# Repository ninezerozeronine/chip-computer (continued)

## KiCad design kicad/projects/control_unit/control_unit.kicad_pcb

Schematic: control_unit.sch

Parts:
C1, C2, C3, C4, C5, C6, C7, C8, C9: 100nF; C_Disc_D4.7mm_W2.5mm_P5.00mm
J1: BUS; PinHeader_1x11_P2.54mm_Horizontal
J2: FLAGS; PinSocket_1x04_P2.54mm_Horizontal
J3: INSTRUCTION; PinSocket_1x08_P2.54mm_Horizontal
J4: BACKPLANE; backplane-connector
J5: MIR INST LEDS; PinSocket_1x16_P2.54mm_Horizontal
J6: STEP LEDS; PinSocket_1x16_P2.54mm_Horizontal
J7: MIR FLAG LEDS; PinSocket_1x08_P2.54mm_Horizontal
J8: STEP RESET; SolderWirePad_1x01_Drill0.8mm
J9: MASTER RESET; PinSocket_1x01_P2.54mm_Horizontal
RN1: MIR INST RESISTORS; R_Array_SIP9
RN2: STEP RESISTORS; R_Array_SIP9
RN3: MIR FLAG RESISTORS; R_Array_SIP5
U1, U2, U3, U4: 28C256; DIP-28_W15.24mm_Socket
U5: 74HCT377; DIP-20_W7.62mm_Socket
U6: 74HCT161; DIP-16_W7.62mm_Socket
U7: 74HCT173; DIP-16_W7.62mm_Socket
U8: 74HCT138; DIP-16_W7.62mm_Socket
U9: 74HCT04; DIP-14_W7.62mm_Socket

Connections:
/CONTROL_CLOCK: J4.34, U5.11 (CP), U6.2 (CP), U7.7 (CP)
/MASTER_RESET: J1.11
/MC_STEP_0: U1.10 (A0), U2.10 (A0), U3.10 (A0), U4.10 (A0), U6.14 (Q0), U8.1 (A)
/MC_STEP_1: U1.9 (A1), U2.9 (A1), U3.9 (A1), U4.9 (A1), U6.13 (Q1), U8.2 (B)
/MC_STEP_2: U1.8 (A2), U2.8 (A2), U3.8 (A2), U4.8 (A2), U6.12 (Q2), U8.3 (C)
/MIR_FLAG_C: J7.5, U1.5 (A5), U2.5 (A5), U3.5 (A5), U4.5 (A5), U7.5 (Q2)
/MIR_FLAG_E: J7.7, U1.4 (A6), U2.4 (A6), U3.4 (A6), U4.4 (A6), U7.6 (Q3)
/MIR_FLAG_N: J7.3, U1.6 (A4), U2.6 (A4), U3.6 (A4), U4.6 (A4), U7.4 (Q1)
/MIR_FLAG_Z: J7.1, U1.7 (A3), U2.7 (A3), U3.7 (A3), U4.7 (A3), U7.3 (Q0)
/MIR_INST_0: J5.1, U1.3 (A7), U2.3 (A7), U3.3 (A7), U4.3 (A7), U5.2 (Q0)
/MIR_INST_1: J5.3, U1.25 (A8), U2.25 (A8), U3.25 (A8), U4.25 (A8), U5.5 (Q1)
/MIR_INST_2: J5.5, U1.24 (A9), U2.24 (A9), U3.24 (A9), U4.24 (A9), U5.6 (Q2)
/MIR_INST_3: J5.7, U1.21 (A10), U2.21 (A10), U3.21 (A10), U4.21 (A10), U5.9 (Q3)
/MIR_INST_4: J5.9, U1.23 (A11), U2.23 (A11), U3.23 (A11), U4.23 (A11), U5.12 (Q4)
/MIR_INST_5: J5.11, U1.2 (A12), U2.2 (A12), U3.2 (A12), U4.2 (A12), U5.15 (Q5)
/MIR_INST_6: J5.13, U1.26 (A13), U2.26 (A13), U3.26 (A13), U4.26 (A13), U5.16 (Q6)
/MIR_INST_7: J5.15, U1.1 (A14), U2.1 (A14), U3.1 (A14), U4.1 (A14), U5.19 (Q7)
/ROM_0_0: J4.1, U1.11 (D0)
/ROM_0_1: J4.2, U1.12 (D1)
/ROM_0_2: J4.3, U1.13 (D2)
/ROM_0_3: J4.4, U1.15 (D3)
/ROM_0_4: J4.5, U1.16 (D4)
/ROM_0_5: J4.6, U1.17 (D5)
/ROM_0_6: J4.7, U1.18 (D6)
/ROM_0_7: J4.8, U1.19 (D7)
/ROM_1_0: J4.9, U2.11 (D0)
/ROM_1_1: J4.10, U2.12 (D1)
/ROM_1_2: J4.11, U2.13 (D2)
/ROM_1_3: J4.12, U2.15 (D3)
/ROM_1_4: J4.13, U2.16 (D4)
/ROM_1_5: J4.14, U2.17 (D5)
/ROM_1_6: J4.15, U2.18 (D6)
/ROM_1_7: J4.16, U2.19 (D7)
/ROM_2_0: J4.17, U3.11 (D0)
/ROM_2_1: J4.18, U3.12 (D1)
/ROM_2_2: J4.19, U3.13 (D2)
/ROM_2_3: J4.20, U3.15 (D3)
/ROM_2_4: J4.21, U3.16 (D4)
/ROM_2_5: J4.22, U3.17 (D5)
/ROM_2_6: J4.23, U3.18 (D6)
/ROM_2_7: J4.24, U3.19 (D7)
/ROM_3_0: J4.25, U4.11 (D0)
/ROM_3_1: J4.26, U4.12 (D1)
/ROM_3_2: J4.27, U4.13 (D2)
/ROM_3_3: J4.28, U4.15 (D3)
/ROM_3_4: J4.29, U4.16 (D4)
/ROM_3_5: J4.30, U4.17 (D5)
/ROM_3_6: J4.31, U4.18 (D6)
/ROM_3_7: J4.32, U4.19 (D7)
GND: C1.1, C2.2, C3.1, C4.2, C5.1, C6.2, C7.2, C8.2, C9.2, J1.10, RN1.1 (common), RN3.1 (common), U1.14 (GND), U1.20 (~CS), U1.22 (~OE), U2.14 (GND), U2.20 (~CS), U2.22 (~OE), U3.14 (GND), U3.20 (~CS), U3.22 (~OE), U4.14 (GND), U4.20 (~CS), U4.22 (~OE), U5.1 (~E), U5.10 (GND), U6.3 (P0), U6.4 (P1), U6.5 (P2), U6.6 (P3), U6.8 (GND), U7.1 (~OE), U7.2 (~OE2), U7.8 (GND), U7.9 (~E1), U7.10 (~E2), U7.15 (MR), U8.4 (~G2A), U8.5 (~G2B), U8.8 (GND), U9.5, U9.7 (GND), U9.9, U9.11, U9.13
unnamed: J2.1, U7.14 (D0)
unnamed: J2.2, U7.13 (D1)
unnamed: J2.3, U7.12 (D2)
unnamed: J2.4, U7.11 (D3)
unnamed: J3.1, U5.3 (D0)
unnamed: J3.2, U5.4 (D1)
unnamed: J3.3, U5.7 (D2)
unnamed: J3.4, U5.8 (D3)
unnamed: J3.5, U5.13 (D4)
unnamed: J3.6, U5.14 (D5)
unnamed: J3.7, U5.17 (D6)
unnamed: J3.8, U5.18 (D7)
unnamed: J5.2, RN1.2 (R1)
unnamed: J5.4, RN1.3 (R2)
unnamed: J5.6, RN1.4 (R3)
unnamed: J5.8, RN1.5 (R4)
unnamed: J5.10, RN1.6 (R5)
unnamed: J5.12, RN1.7 (R6)
unnamed: J5.14, RN1.8 (R7)
unnamed: J5.16, RN1.9 (R8)
unnamed: J6.1, U8.15 (Y0)
unnamed: J6.2, RN2.2 (R1)
unnamed: J6.3, U8.14 (Y1)
unnamed: J6.4, RN2.3 (R2)
unnamed: J6.5, U8.13 (Y2)
unnamed: J6.6, RN2.4 (R3)
unnamed: J6.7, U8.12 (Y3)
unnamed: J6.8, RN2.5 (R4)
unnamed: J6.9, U8.11 (Y4)
unnamed: J6.10, RN2.6 (R5)
unnamed: J6.11, U8.10 (Y5)
unnamed: J6.12, RN2.7 (R6)
unnamed: J6.13, U8.9 (Y6)
unnamed: J6.14, RN2.8 (R7)
unnamed: J6.15, U8.7 (Y7)
unnamed: J6.16, RN2.9 (R8)
unnamed: J7.2, RN3.2 (R1)
unnamed: J7.4, RN3.3 (R2)
unnamed: J7.6, RN3.4 (R3)
unnamed: J7.8, RN3.5 (R4)
unnamed: J8.1, U9.3
unnamed: J9.1, U9.1
unnamed: U6.1 (~MR), U9.2
unnamed: U6.9 (~SPE), U9.4
VCC: C1.2, C2.1, C3.2, C4.1, C5.2, C6.1, C7.1, C8.1, C9.1, J1.9, RN2.1 (common), U1.27 (~WE), U1.28 (VCC), U2.27 (~WE), U2.28 (VCC), U3.27 (~WE), U3.28 (VCC), U4.27 (~WE), U4.28 (VCC), U5.20 (VCC), U6.7 (PE), U6.10 (TE), U6.16 (VCC), U7.16 (VCC), U8.6 (G1), U8.16 (VCC), U9.14 (VCC)

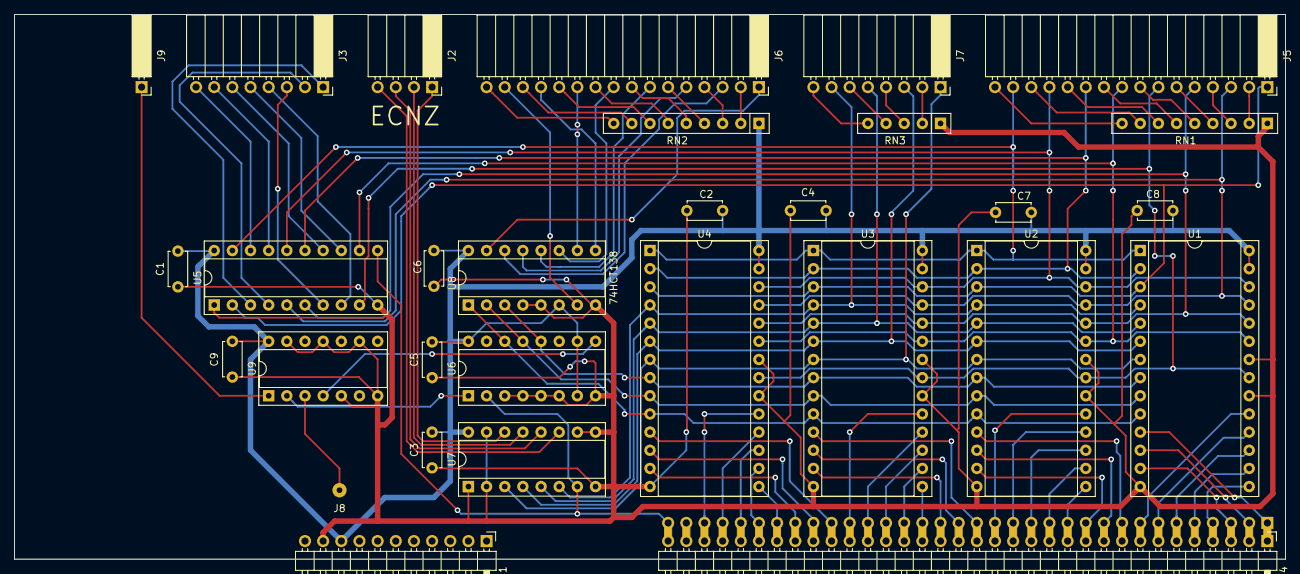
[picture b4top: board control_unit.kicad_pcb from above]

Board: 2 copper layers, 177.8 x 76.2 mm, 30 parts (0 on the bottom side), 94 nets.

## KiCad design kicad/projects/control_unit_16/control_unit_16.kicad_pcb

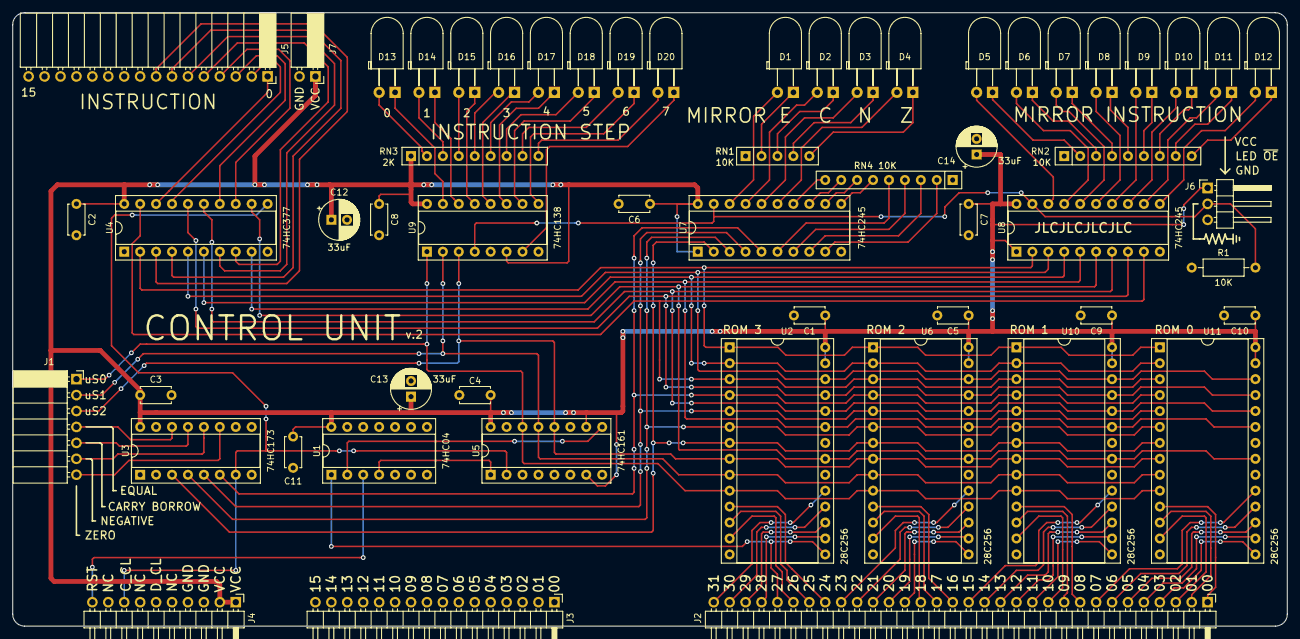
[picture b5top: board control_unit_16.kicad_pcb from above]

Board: 2 copper layers, 203.2 x 97.8 mm, 57 parts (0 on the bottom side), 114 nets.

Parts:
C1, C2, C3, C4, C5, C6, C7, C8, C9, C10, C11: 0.1uF; C_Disc_D4.7mm_W2.5mm_P5.00mm
C12, C13, C14: 33uF; CP_Radial_D6.3mm_P2.50mm
D1, D2, D3, D4, D5, D6, D7, D8, D9, D10, D11, D12, D13, D14, D15, D16, D17, D18, D19, D20: LED; LED_D5.0mm_Horizontal_O3.81mm_Z3.0mm
J1: Conn_01x04_Female; PinSocket_1x07_P2.54mm_Horizontal
J2: Control_signal_backplane; backplane-connector-single-row
J3: Bus_connection; bus-connection
J4: Aux_connection; aux-connection
J5: Conn_01x16_Female; PinSocket_1x16_P2.54mm_Horizontal
J6: LED_CONTROL; PinHeader_1x03_P2.54mm_Horizontal
J7: TOP_POWER; PinSocket_1x02_P2.54mm_Horizontal
R1: 10K; R_Axial_DIN0207_L6.3mm_D2.5mm_P10.16mm_Horizontal
RN1: 10K; R_Array_SIP5
RN2, RN4: 10K; R_Array_SIP9
RN3: 2K; R_Array_SIP9
U1: 74HC04; DIP-14_W7.62mm_Socket
U2, U6, U10, U11: 28C256; DIP-28_W15.24mm_Socket
U3: 74HC173; DIP-16_W7.62mm_Socket
U4: 74HC377; DIP-20_W7.62mm_Socket
U5: 74HC161; DIP-16_W7.62mm_Socket
U7, U8: 74HC245; DIP-20_W7.62mm_Socket
U9: 74HC138; DIP-16_W7.62mm_Socket

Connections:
/BIN_STEP_0: J1.1, U2.10, U5.14, U6.10, U9.1, U10.10, U11.10
/BIN_STEP_1: J1.2, U2.9, U5.13, U6.9, U9.2, U10.9, U11.9
/BIN_STEP_2: J1.3, U2.8, U5.12, U6.8, U9.3, U10.8, U11.8
/CARRY: J1.5, U3.13
/CONTROL_CLOCK: J4.8, U3.7, U4.11, U5.2
/EQUAL: J1.4, U3.14
/INST_00: J5.1, U4.18
/INST_01: J5.2, U4.17
/INST_02: J5.3, U4.14
/INST_03: J5.4, U4.13
/INST_04: J5.5, U4.8
/INST_05: J5.6, U4.7
/INST_06: J5.7, U4.4
/INST_07: J5.8, U4.3
/LED_CONTROL: J6.2, R1.2, U7.19, U8.19, U9.4
/LIN_STEP_0: D13.1, U9.15
/LIN_STEP_1: D14.1, U9.14
/LIN_STEP_2: D15.1, U9.13
/LIN_STEP_3: D16.1, U9.12
/LIN_STEP_4: D17.1, U9.11
/LIN_STEP_5: D18.1, U9.10
/LIN_STEP_6: D19.1, U9.9
/LIN_STEP_7: D20.1, U9.7
/MIR_CARRY: U2.6, U3.4, U6.6, U7.3, U10.6, U11.6
/MIR_EQUAL: U2.7, U3.3, U6.7, U7.2, U10.7, U11.7
/MIR_INST_0: U2.3, U4.19, U6.3, U8.9, U10.3, U11.3
/MIR_INST_1: U2.25, U4.16, U6.25, U8.8, U10.25, U11.25
/MIR_INST_2: U2.24, U4.15, U6.24, U8.7, U10.24, U11.24
/MIR_INST_3: U2.21, U4.12, U6.21, U8.6, U10.21, U11.21
/MIR_INST_4: U2.23, U4.9, U6.23, U8.5, U10.23, U11.23
/MIR_INST_5: U2.2, U4.6, U6.2, U8.4, U10.2, U11.2
/MIR_INST_6: U2.26, U4.5, U6.26, U8.3, U10.26, U11.26
/MIR_INST_7: U2.1, U4.2, U6.1, U8.2, U10.1, U11.1
/MIR_NEGATIVE: U2.5, U3.5, U6.5, U7.4, U10.5, U11.5
/MIR_ZERO: U2.4, U3.6, U6.4, U7.5, U10.4, U11.4
/NEGATIVE: J1.6, U3.12
/RESET: J4.10, U1.3
/ROM_0_0: J2.1, U11.11
/ROM_0_1: J2.2, U11.12
/ROM_0_2: J2.3, U11.13
/ROM_0_3: J2.4, U11.15
/ROM_0_4: J2.5, U11.16
/ROM_0_5: J2.6, U11.17
/ROM_0_6: J2.7, U11.18
/ROM_0_7: J2.8, U11.19
/ROM_1_0: J2.9, U10.11
/ROM_1_1: J2.10, U10.12
/ROM_1_2: J2.11, U10.13
/ROM_1_3: J2.12, U10.15
/ROM_1_4: J2.13, U10.16
/ROM_1_5: J2.14, U10.17
/ROM_1_6: J2.15, U10.18
/ROM_1_7: J2.16, U10.19
/ROM_2_0: J2.17, U6.11
/ROM_2_1: J2.18, U6.12
/ROM_2_2: J2.19, U6.13
/ROM_2_3: J2.20, U6.15
/ROM_2_4: J2.21, U6.16
/ROM_2_5: J2.22, U6.17
/ROM_2_6: J2.23, U6.18
/ROM_2_7: J2.24, U6.19
/ROM_3_0: J2.25, U2.11
/ROM_3_1: J2.26, U2.12
/ROM_3_2: J2.27, U2.13
/ROM_3_4: J2.29, U2.16
/ROM_3_5: J2.30, U2.17
/ROM_3_6: J2.31, U2.18
/ROM_3_7: J2.32, U2.19
/STEP_RESET: J2.28, U1.1, U2.15
/ZERO: J1.7, U3.11
/~RESET: U1.4, U5.1
/~STEP_RESET: U1.2, U5.9
GND: C1.2, C2.2, C3.2, C4.2, C5.2, C6.2, C7.2, C8.2, C9.2, C10.2, C11.2, C12.2, C13.2, C14.2, J4.3, J4.4, J6.3, J7.2, R1.1, RN1.1, RN2.1, RN4.1, U1.5, U1.7, U1.9, U1.11, U1.13, U2.14, U2.20, U2.22, U3.1, U3.2, U3.8, U3.9, U3.10, U3.15, U4.1, U4.10, U5.3, U5.4, U5.5, U5.6, U5.8, U6.14, U6.20, U6.22, U7.10, U8.10, U9.5, U9.8, U10.14, U10.20, U10.22, U11.14, U11.20, U11.22
unnamed: D1.1, RN1.2
unnamed: D1.2, U7.18
unnamed: D2.1, RN1.3
unnamed: D2.2, U7.17
unnamed: D3.1, RN1.4
unnamed: D3.2, U7.16
unnamed: D4.1, RN1.5
unnamed: D4.2, U7.15
unnamed: D5.1, RN2.2
unnamed: D5.2, U8.18
unnamed: D6.1, RN2.3
unnamed: D6.2, U8.17
unnamed: D7.1, RN2.4
unnamed: D7.2, U8.16
unnamed: D8.1, RN2.5
unnamed: D8.2, U8.15
unnamed: D9.1, RN2.6
unnamed: D9.2, U8.14
unnamed: D10.1, RN2.7
unnamed: D10.2, U8.13
unnamed: D11.1, RN2.8
unnamed: D11.2, U8.12
unnamed: D12.1, RN2.9
unnamed: D12.2, U8.11
unnamed: D13.2, RN3.2
unnamed: D14.2, RN3.3
unnamed: D15.2, RN3.4
unnamed: D16.2, RN3.5
unnamed: D17.2, RN3.6
unnamed: D18.2, RN3.7
unnamed: D19.2, RN3.8
unnamed: D20.2, RN3.9
unnamed: RN4.2, U7.9
unnamed: RN4.3, U7.8
unnamed: RN4.4, U7.7
unnamed: RN4.5, U7.6
unnamed: RN4.6, U7.11
unnamed: RN4.7, U7.12
unnamed: RN4.8, U7.13
unnamed: RN4.9, U7.14
VCC: C1.1, C2.1, C3.1, C4.1, C5.1, C6.1, C7.1, C8.1, C9.1, C10.1, C11.1, C12.1, C13.1, C14.1, J4.1, J4.2, J6.1, J7.1, RN3.1, U1.14, U2.27, U2.28, U3.16, U4.20, U5.7, U5.10, U5.16, U6.27, U6.28, U7.1, U7.20, U8.1, U8.20, U9.6, U9.16, U10.27, U10.28, U11.27, U11.28

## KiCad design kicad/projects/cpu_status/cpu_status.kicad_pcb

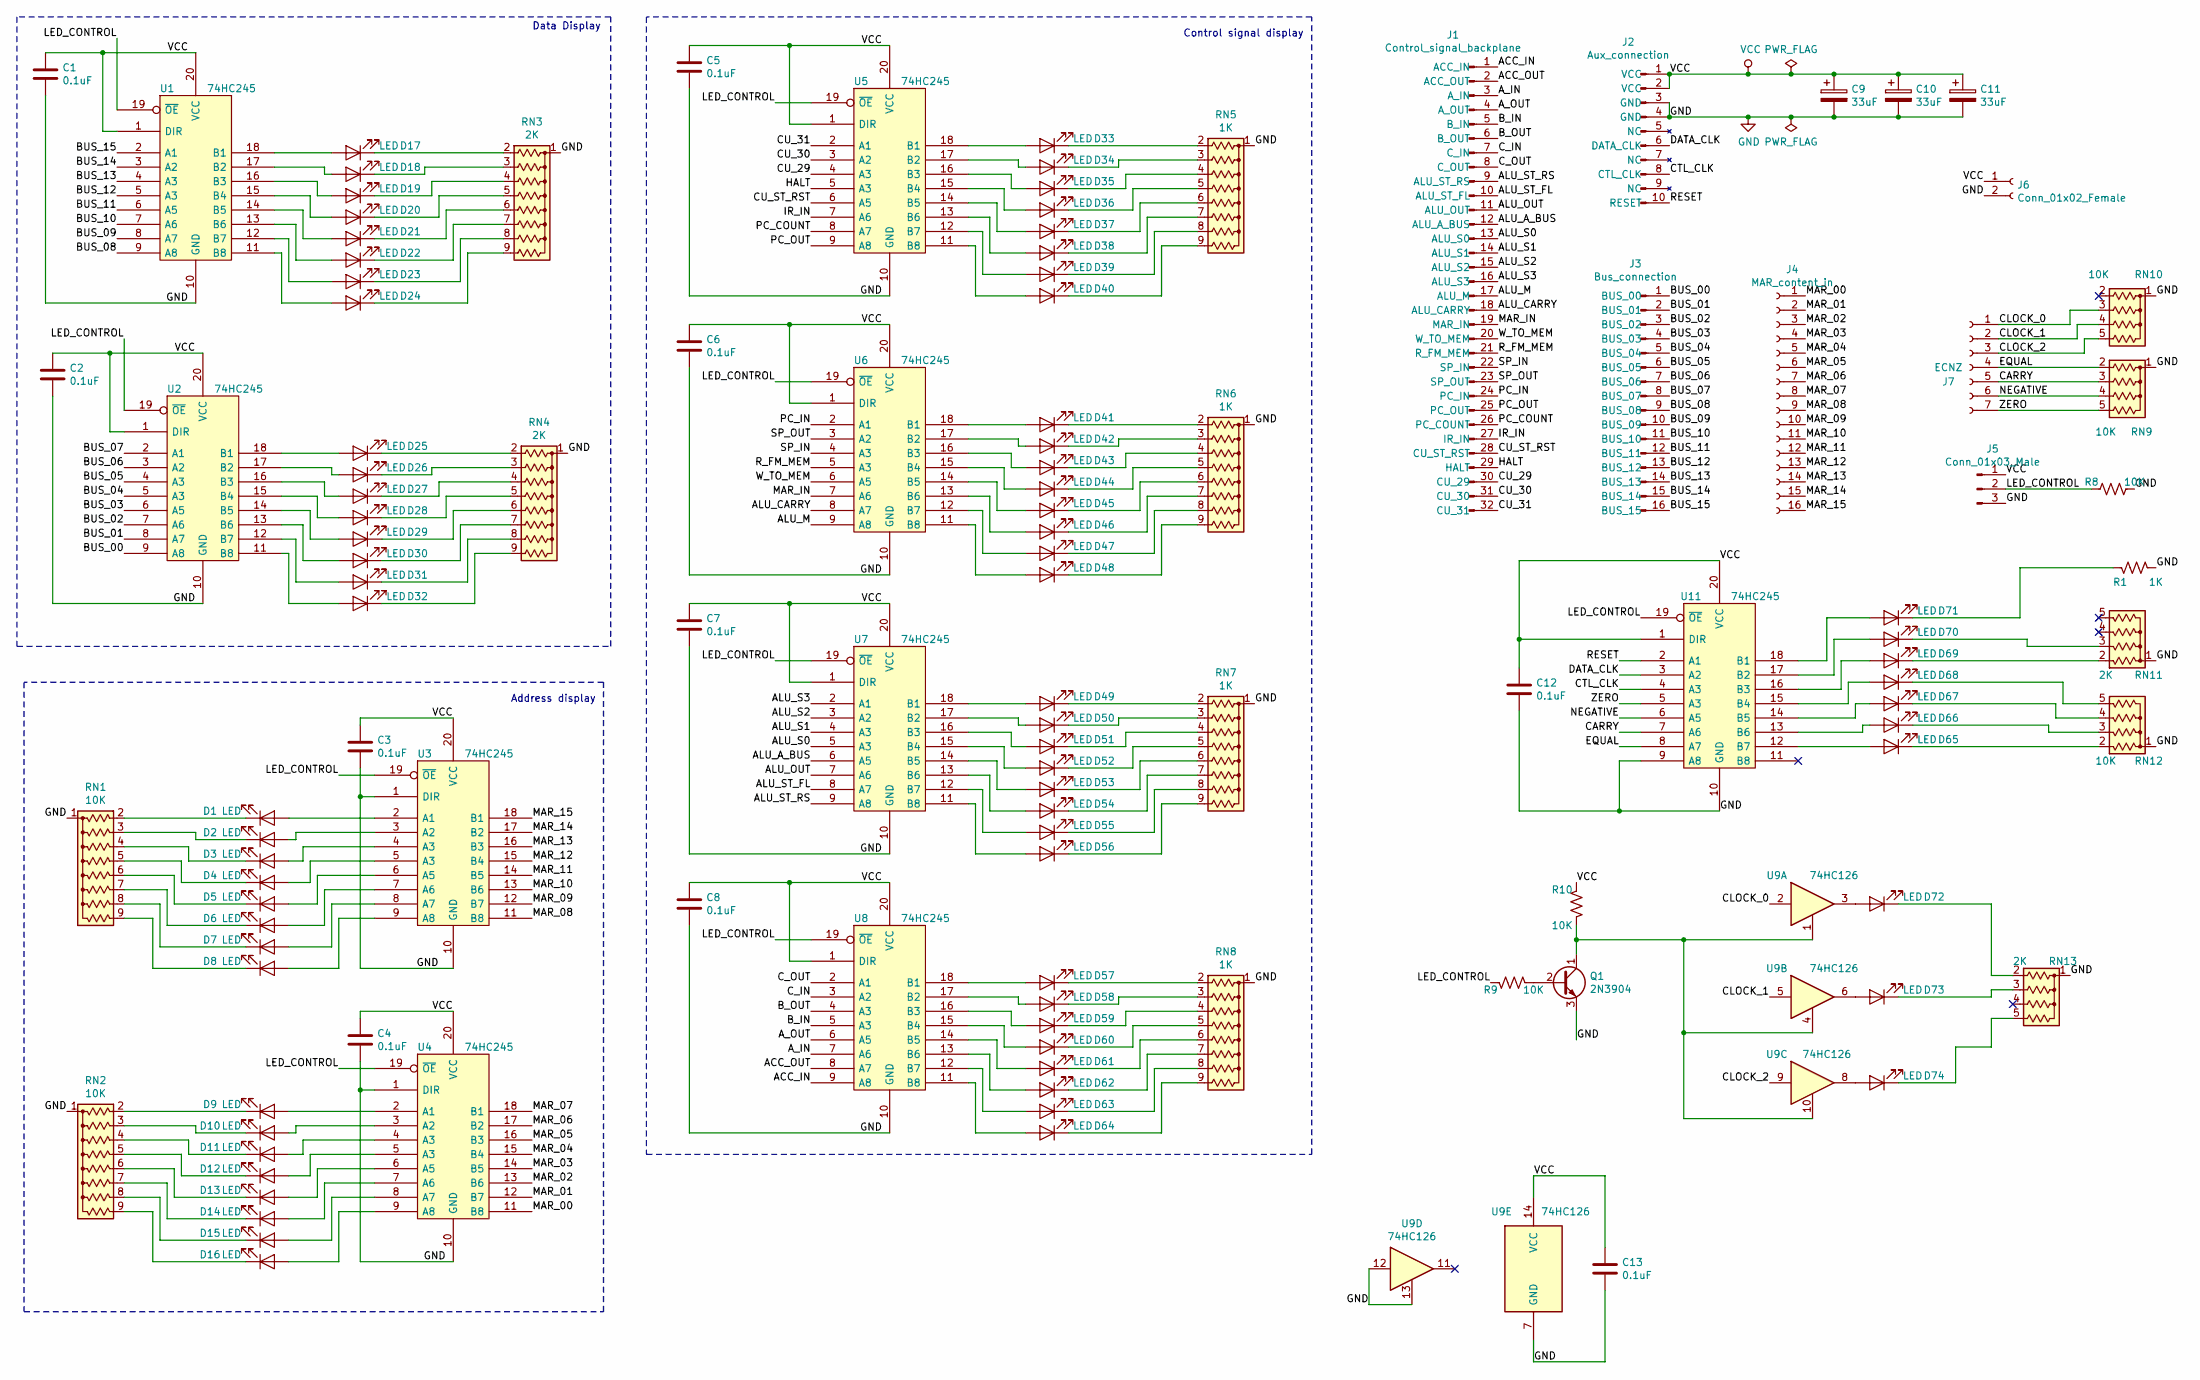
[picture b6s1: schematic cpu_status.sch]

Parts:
C1, C2, C3, C4, C5, C6, C7, C8, C12, C13: 0.1uF; C_Disc_D4.7mm_W2.5mm_P5.00mm
C9, C10, C11: 33uF; CP_Radial_D6.3mm_P2.50mm
D1, D2, D3, D4, D5, D6, D7, D8, D9, D10, D11, D12, D13, D14, D15, D16, D17, D18, D19, D20, D21, D22, D23, D24, D25, D26, D27, D28, D29, D30, D31, D32, D33, D34, D35, D36, D37, D38, D39, D40, D41, D42, D43, D44, D45, D46, D47, D48, D49, D50, D51, D52, D53, D54, D55, D56, D57, D58, D59, D60, D61, D62, D63, D64, D65, D66, D67, D68, D69, D70, D71, D72, D73, D74: LED; LED_D5.0mm
J1: Control_signal_backplane; backplane-connector-single-row
J2: Aux_connection; aux-connection
J3: Bus_connection; bus-connection
J4: MAR_content_in; PinSocket_1x16_P2.54mm_Horizontal
J5: Conn_01x03_Male; PinHeader_1x03_P2.54mm_Horizontal
J6: Conn_01x02_Female; PinSocket_1x02_P2.54mm_Horizontal
J7: ECNZ; PinSocket_1x07_P2.54mm_Horizontal
Q1: 2N3904; TO-92L_Inline_Wide
R1: 1K; R_Axial_DIN0207_L6.3mm_D2.5mm_P10.16mm_Horizontal
R8: 10K; R_Axial_DIN0207_L6.3mm_D2.5mm_P10.16mm_Horizontal
R9, R10: 10K; R_Axial_DIN0207_L6.3mm_D2.5mm_P2.54mm_Vertical
RN1, RN2: 10K; R_Array_SIP9
RN3, RN4: 2K; R_Array_SIP9
RN5, RN6, RN7, RN8: 1K; R_Array_SIP9
RN9, RN10, RN12: 10K; R_Array_SIP5
RN11, RN13: 2K; R_Array_SIP5
U1, U2, U3, U4, U5, U6, U7, U8, U11: 74HC245; DIP-20_W7.62mm_Socket
U9: 74HC126; DIP-14_W7.62mm_Socket

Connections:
/ACC_IN: J1.1 (ACC_IN), U8.9 (A8)
/ACC_OUT: J1.2 (ACC_OUT), U8.8 (A7)
/ALU_A_BUS: J1.12 (ALU_A_BUS), U7.6 (A5)
/ALU_CARRY: J1.18 (ALU_CARRY), U6.8 (A7)
/ALU_M: J1.17 (ALU_M), U6.9 (A8)
/ALU_OUT: J1.11 (ALU_OUT), U7.7 (A6)
/ALU_S0: J1.13 (ALU_S0), U7.5 (A3)
/ALU_S1: J1.14 (ALU_S1), U7.4 (A3)
/ALU_S2: J1.15 (ALU_S2), U7.3 (A2)
/ALU_S3: J1.16 (ALU_S3), U7.2 (A1)
/ALU_ST_FL: J1.10 (ALU_ST_FL), U7.8 (A7)
/ALU_ST_RS: J1.9 (ALU_ST_RS), U7.9 (A8)
/A_IN: J1.3 (A_IN), U8.7 (A6)
/A_OUT: J1.4 (A_OUT), U8.6 (A5)
/BUS_00: J3.1 (BUS_00), U2.9 (A8)
/BUS_01: J3.2 (BUS_01), U2.8 (A7)
/BUS_02: J3.3 (BUS_02), U2.7 (A6)
/BUS_03: J3.4 (BUS_03), U2.6 (A5)
/BUS_04: J3.5 (BUS_04), U2.5 (A3)
/BUS_05: J3.6 (BUS_05), U2.4 (A3)
/BUS_06: J3.7 (BUS_06), U2.3 (A2)
/BUS_07: J3.8 (BUS_07), U2.2 (A1)
/BUS_08: J3.9 (BUS_08), U1.9 (A8)
/BUS_09: J3.10 (BUS_09), U1.8 (A7)
/BUS_10: J3.11 (BUS_10), U1.7 (A6)
/BUS_11: J3.12 (BUS_11), U1.6 (A5)
/BUS_12: J3.13 (BUS_12), U1.5 (A3)
/BUS_13: J3.14 (BUS_13), U1.4 (A3)
/BUS_14: J3.15 (BUS_14), U1.3 (A2)
/BUS_15: J3.16 (BUS_15), U1.2 (A1)
/B_IN: J1.5 (B_IN), U8.5 (A3)
/B_OUT: J1.6 (B_OUT), U8.4 (A3)
/CARRY: J7.5, RN9.3 (R2), U11.7 (A6)
/CLOCK_0: J7.1, RN10.3 (R2), U9.2
/CLOCK_1: J7.2, RN10.4 (R3), U9.5
/CLOCK_2: J7.3, RN10.5 (R4), U9.9
/CTL_CLK: J2.8 (CTL_CLK), U11.4 (A3)
/CU_29: J1.30 (CU_29), U5.4 (A3)
/CU_30: J1.31 (CU_30), U5.3 (A2)
/CU_31: J1.32 (CU_31), U5.2 (A1)
/CU_ST_RST: J1.28 (CU_ST_RST), U5.6 (A5)
/C_IN: J1.7 (C_IN), U8.3 (A2)
/C_OUT: J1.8 (C_OUT), U8.2 (A1)
/DATA_CLK: J2.6 (DATA_CLK), U11.3 (A2)
/EQUAL: J7.4, RN9.2 (R1), U11.8 (A7)
/HALT: J1.29 (HALT), U5.5 (A3)
/IR_IN: J1.27 (IR_IN), U5.7 (A6)
/LED_CONTROL: J5.2, R8.2, R9.2, U1.19 (~OE), U2.19 (~OE), U3.19 (~OE), U4.19 (~OE), U5.19 (~OE), U6.19 (~OE), U7.19 (~OE), U8.19 (~OE), U11.19 (~OE)
/MAR_00: J4.1, U4.11 (B8)
/MAR_01: J4.2, U4.12 (B7)
/MAR_02: J4.3, U4.13 (B6)
/MAR_03: J4.4, U4.14 (B5)
/MAR_04: J4.5, U4.15 (B4)
/MAR_05: J4.6, U4.16 (B3)
/MAR_06: J4.7, U4.17 (B2)
/MAR_07: J4.8, U4.18 (B1)
/MAR_08: J4.9, U3.11 (B8)
/MAR_09: J4.10, U3.12 (B7)
/MAR_10: J4.11, U3.13 (B6)
/MAR_11: J4.12, U3.14 (B5)
/MAR_12: J4.13, U3.15 (B4)
/MAR_13: J4.14, U3.16 (B3)
/MAR_14: J4.15, U3.17 (B2)
/MAR_15: J4.16, U3.18 (B1)
/MAR_IN: J1.19 (MAR_IN), U6.7 (A6)
/NEGATIVE: J7.6, RN9.4 (R3), U11.6 (A5)
/PC_COUNT: J1.26 (PC_COUNT), U5.8 (A7)
/PC_IN: J1.24 (PC_IN), U6.2 (A1)
/PC_OUT: J1.25 (PC_OUT), U5.9 (A8)
/RESET: J2.10 (RESET), U11.2 (A1)
/R_FM_MEM: J1.21 (R_FM_MEM), U6.5 (A3)
/SP_IN: J1.22 (SP_IN), U6.4 (A3)
/SP_OUT: J1.23 (SP_OUT), U6.3 (A2)
/W_TO_MEM: J1.20 (W_TO_MEM), U6.6 (A5)
/ZERO: J7.7, RN9.5 (R4), U11.5 (A3)
GND: C1.2, C2.2, C3.2, C4.2, C5.2, C6.2, C7.2, C8.2, C9.2, C10.2, C11.2, C12.2, C13.2, J2.3 (GND), J2.4 (GND), J5.3, J6.2, Q1.3 (E), R1.1, R8.1, RN1.1 (common), RN2.1 (common), RN3.1 (common), RN4.1 (common), RN5.1 (common), RN6.1 (common), RN7.1 (common), RN8.1 (common), RN9.1 (common), RN10.1 (common), RN11.1 (common), RN12.1 (common), RN13.1 (common), U1.10 (GND), U2.10 (GND), U3.1 (DIR), U3.10 (GND), U4.1 (DIR), U4.10 (GND), U5.10 (GND), U6.10 (GND), U7.10 (GND), U8.10 (GND), U9.7 (GND), U9.12, U9.13, U11.9 (A8), U11.10 (GND)
unnamed: D1.1 (K), RN1.2 (R1)
unnamed: D1.2 (A), U3.2 (A1)
unnamed: D2.1 (K), RN1.3 (R2)
unnamed: D2.2 (A), U3.3 (A2)
unnamed: D3.1 (K), RN1.4 (R3)
unnamed: D3.2 (A), U3.4 (A3)
unnamed: D4.1 (K), RN1.5 (R4)
unnamed: D4.2 (A), U3.5 (A3)
unnamed: D5.1 (K), RN1.6 (R5)
unnamed: D5.2 (A), U3.6 (A5)
unnamed: D6.1 (K), RN1.7 (R6)
unnamed: D6.2 (A), U3.7 (A6)
unnamed: D7.1 (K), RN1.8 (R7)
unnamed: D7.2 (A), U3.8 (A7)
unnamed: D8.1 (K), RN1.9 (R8)
unnamed: D8.2 (A), U3.9 (A8)
unnamed: D9.1 (K), RN2.2 (R1)
unnamed: D9.2 (A), U4.2 (A1)
unnamed: D10.1 (K), RN2.3 (R2)
unnamed: D10.2 (A), U4.3 (A2)
unnamed: D11.1 (K), RN2.4 (R3)
unnamed: D11.2 (A), U4.4 (A3)
unnamed: D12.1 (K), RN2.5 (R4)
unnamed: D12.2 (A), U4.5 (A3)
unnamed: D13.1 (K), RN2.6 (R5)
unnamed: D13.2 (A), U4.6 (A5)
unnamed: D14.1 (K), RN2.7 (R6)
unnamed: D14.2 (A), U4.7 (A6)
unnamed: D15.1 (K), RN2.8 (R7)
unnamed: D15.2 (A), U4.8 (A7)
unnamed: D16.1 (K), RN2.9 (R8)
unnamed: D16.2 (A), U4.9 (A8)
unnamed: D17.1 (K), RN3.2 (R1)
unnamed: D17.2 (A), U1.18 (B1)
unnamed: D18.1 (K), RN3.3 (R2)
unnamed: D18.2 (A), U1.17 (B2)
unnamed: D19.1 (K), RN3.4 (R3)
unnamed: D19.2 (A), U1.16 (B3)
unnamed: D20.1 (K), RN3.5 (R4)
unnamed: D20.2 (A), U1.15 (B4)
unnamed: D21.1 (K), RN3.6 (R5)
unnamed: D21.2 (A), U1.14 (B5)
unnamed: D22.1 (K), RN3.7 (R6)
unnamed: D22.2 (A), U1.13 (B6)
unnamed: D23.1 (K), RN3.8 (R7)
unnamed: D23.2 (A), U1.12 (B7)
unnamed: D24.1 (K), RN3.9 (R8)
unnamed: D24.2 (A), U1.11 (B8)
unnamed: D25.1 (K), RN4.2 (R1)
unnamed: D25.2 (A), U2.18 (B1)
unnamed: D26.1 (K), RN4.3 (R2)
unnamed: D26.2 (A), U2.17 (B2)
unnamed: D27.1 (K), RN4.4 (R3)
unnamed: D27.2 (A), U2.16 (B3)
unnamed: D28.1 (K), RN4.5 (R4)
unnamed: D28.2 (A), U2.15 (B4)
unnamed: D29.1 (K), RN4.6 (R5)
unnamed: D29.2 (A), U2.14 (B5)
unnamed: D30.1 (K), RN4.7 (R6)
unnamed: D30.2 (A), U2.13 (B6)
unnamed: D31.1 (K), RN4.8 (R7)
unnamed: D31.2 (A), U2.12 (B7)
unnamed: D32.1 (K), RN4.9 (R8)
unnamed: D32.2 (A), U2.11 (B8)
unnamed: D33.1 (K), RN5.2 (R1)
unnamed: D33.2 (A), U5.18 (B1)
unnamed: D34.1 (K), RN5.3 (R2)
unnamed: D34.2 (A), U5.17 (B2)
unnamed: D35.1 (K), RN5.4 (R3)
unnamed: D35.2 (A), U5.16 (B3)
unnamed: D36.1 (K), RN5.5 (R4)
unnamed: D36.2 (A), U5.15 (B4)
unnamed: D37.1 (K), RN5.6 (R5)
unnamed: D37.2 (A), U5.14 (B5)
unnamed: D38.1 (K), RN5.7 (R6)
unnamed: D38.2 (A), U5.13 (B6)
unnamed: D39.1 (K), RN5.8 (R7)
unnamed: D39.2 (A), U5.12 (B7)
unnamed: D40.1 (K), RN5.9 (R8)
unnamed: D40.2 (A), U5.11 (B8)
unnamed: D41.1 (K), RN6.2 (R1)
unnamed: D41.2 (A), U6.18 (B1)
unnamed: D42.1 (K), RN6.3 (R2)
unnamed: D42.2 (A), U6.17 (B2)
unnamed: D43.1 (K), RN6.4 (R3)
unnamed: D43.2 (A), U6.16 (B3)
unnamed: D44.1 (K), RN6.5 (R4)
unnamed: D44.2 (A), U6.15 (B4)
unnamed: D45.1 (K), RN6.6 (R5)
unnamed: D45.2 (A), U6.14 (B5)
unnamed: D46.1 (K), RN6.7 (R6)
unnamed: D46.2 (A), U6.13 (B6)
unnamed: D47.1 (K), RN6.8 (R7)
unnamed: D47.2 (A), U6.12 (B7)
unnamed: D48.1 (K), RN6.9 (R8)
unnamed: D48.2 (A), U6.11 (B8)
unnamed: D49.1 (K), RN7.2 (R1)
unnamed: D49.2 (A), U7.18 (B1)
unnamed: D50.1 (K), RN7.3 (R2)
unnamed: D50.2 (A), U7.17 (B2)
unnamed: D51.1 (K), RN7.4 (R3)
unnamed: D51.2 (A), U7.16 (B3)
unnamed: D52.1 (K), RN7.5 (R4)
unnamed: D52.2 (A), U7.15 (B4)
unnamed: D53.1 (K), RN7.6 (R5)
unnamed: D53.2 (A), U7.14 (B5)
unnamed: D54.1 (K), RN7.7 (R6)
unnamed: D54.2 (A), U7.13 (B6)
unnamed: D55.1 (K), RN7.8 (R7)
unnamed: D55.2 (A), U7.12 (B7)
unnamed: D56.1 (K), RN7.9 (R8)
unnamed: D56.2 (A), U7.11 (B8)
unnamed: D57.1 (K), RN8.2 (R1)
unnamed: D57.2 (A), U8.18 (B1)
unnamed: D58.1 (K), RN8.3 (R2)
unnamed: D58.2 (A), U8.17 (B2)
unnamed: D59.1 (K), RN8.4 (R3)
unnamed: D59.2 (A), U8.16 (B3)
unnamed: D60.1 (K), RN8.5 (R4)
unnamed: D60.2 (A), U8.15 (B4)
unnamed: D61.1 (K), RN8.6 (R5)
unnamed: D61.2 (A), U8.14 (B5)
unnamed: D62.1 (K), RN8.7 (R6)
unnamed: D62.2 (A), U8.13 (B6)
unnamed: D63.1 (K), RN8.8 (R7)
unnamed: D63.2 (A), U8.12 (B7)
unnamed: D64.1 (K), RN8.9 (R8)
unnamed: D64.2 (A), U8.11 (B8)
unnamed: D65.1 (K), RN12.2 (R1)
unnamed: D65.2 (A), U11.12 (B7)
unnamed: D66.1 (K), RN12.3 (R2)
unnamed: D66.2 (A), U11.13 (B6)
unnamed: D67.1 (K), RN12.4 (R3)
unnamed: D67.2 (A), U11.14 (B5)
unnamed: D68.1 (K), RN12.5 (R4)
unnamed: D68.2 (A), U11.15 (B4)
unnamed: D69.1 (K), RN11.2 (R1)
unnamed: D69.2 (A), U11.16 (B3)
unnamed: D70.1 (K), RN11.3 (R2)
unnamed: D70.2 (A), U11.17 (B2)
unnamed: D71.1 (K), R1.2
unnamed: D71.2 (A), U11.18 (B1)
unnamed: D72.1 (K), RN13.2 (R1)
unnamed: D72.2 (A), U9.3
unnamed: D73.1 (K), RN13.3 (R2)
unnamed: D73.2 (A), U9.6
unnamed: D74.1 (K), RN13.5 (R4)
unnamed: D74.2 (A), U9.8
unnamed: Q1.1 (C), R10.1, U9.1, U9.4, U9.10
unnamed: Q1.2 (B), R9.1
VCC: C1.1, C2.1, C3.1, C4.1, C5.1, C6.1, C7.1, C8.1, C9.1, C10.1, C11.1, C12.1, C13.1, J2.1 (VCC), J2.2 (VCC), J5.1, J6.1, R10.2, U1.1 (DIR), U1.20 (VCC), U2.1 (DIR), U2.20 (VCC), U3.20 (VCC), U4.20 (VCC), U5.1 (DIR), U5.20 (VCC), U6.1 (DIR), U6.20 (VCC), U7.1 (DIR), U7.20 (VCC), U8.1 (DIR), U8.20 (VCC), U9.14 (VCC), U11.1 (DIR), U11.20 (VCC)

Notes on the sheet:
Address display
Data Display
Control signal display

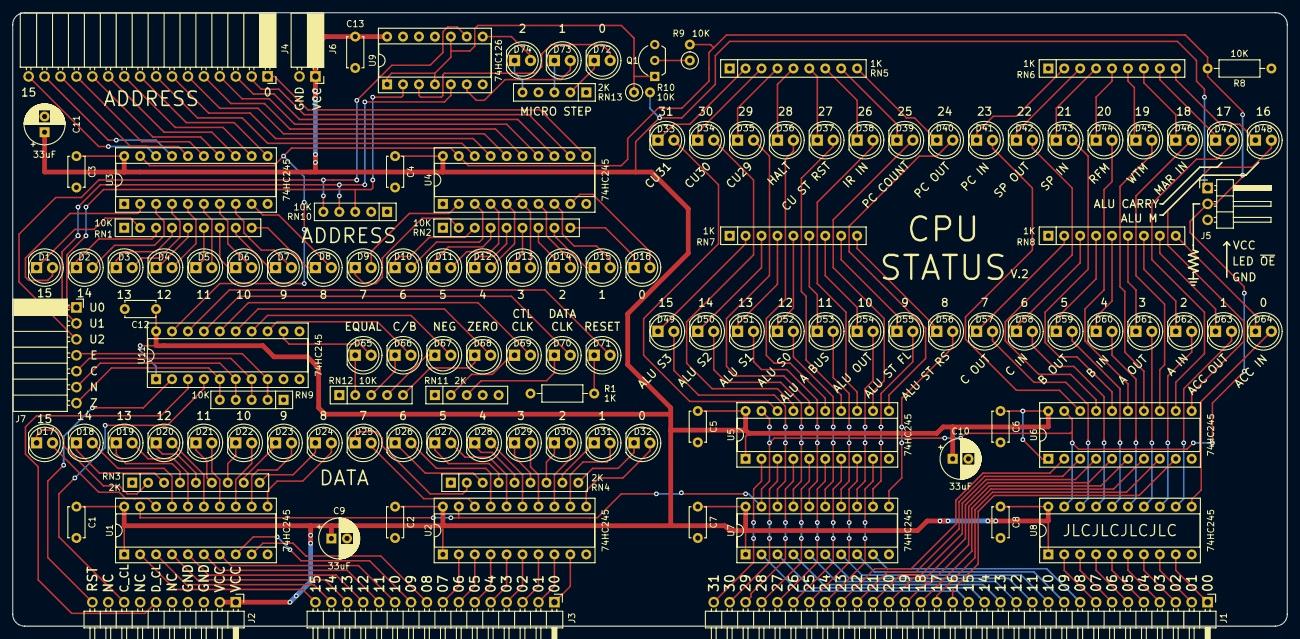
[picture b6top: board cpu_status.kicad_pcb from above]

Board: 2 copper layers, 203.2 x 97.8 mm, 122 parts (0 on the bottom side), 227 nets.
